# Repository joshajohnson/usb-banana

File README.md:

# Banana to USB Adaptor

PCB to adapt banana plugs found on most power supplies to a female USB A connector. 

## Parts Required
- 1 x Molex 105057-0001 USB Connnector [Mouser](https://www.mouser.com/ProductDetail/538-105057-0001) [Digikey](https://www.digikey.com/products/en?keywords=%20105057-0001%20)
- 2 x Screw in Banana Plugs [Mouser](https://www.mouser.com/ProductDetail/565-72918) [Digikey](https://www.digikey.com/product-detail/en/pomona-electronics/72918/501-1200-ND/1196334)
- Optional: 0603 resistor (max 200 ohms) to comply with USB Battery Charging Spec ([Rev 1.2, page 45](https://web.archive.org/web/20141006113700/http://www.usb.org/developers/docs/devclass_docs/BCv1.2_070312.zip))

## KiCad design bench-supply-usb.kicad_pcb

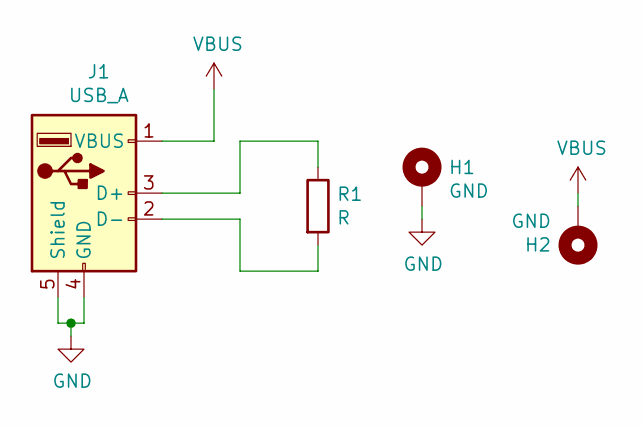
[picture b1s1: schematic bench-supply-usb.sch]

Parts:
H1, H2: GND; MountingHole_3.2mm_M3_Pad_Via
J1: USB_A; USB_A_Molex_105057_Vertical
R1: R; R_0603_1608Metric

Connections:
GND: H1.1, J1.4 (GND), J1.5 (Shield)
unnamed: J1.2 (D-), R1.2
unnamed: J1.3 (D+), R1.1
VBUS: H2.1, J1.1 (VBUS)

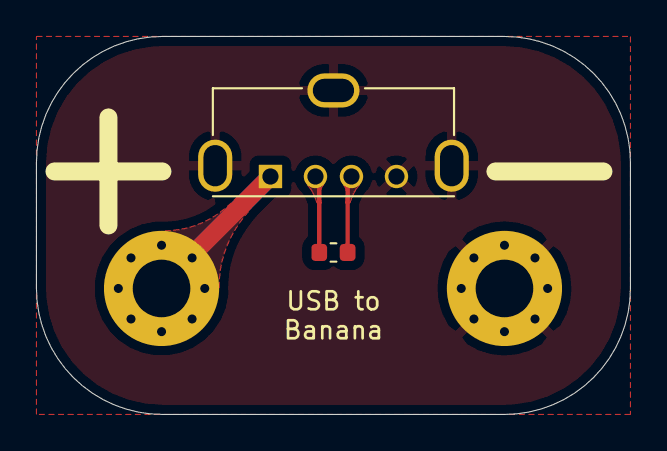
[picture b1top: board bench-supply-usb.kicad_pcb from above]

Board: 2 copper layers, 33.0 x 21.0 mm, 4 parts (0 on the bottom side), 4 nets.

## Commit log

2020-01-16 add files + gerbers
2020-01-16 attempt to fix image
2020-01-16 fix mouser links
